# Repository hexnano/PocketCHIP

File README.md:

# PocketCHIP
PocketCHIP GSM+Camera Addon with A6C

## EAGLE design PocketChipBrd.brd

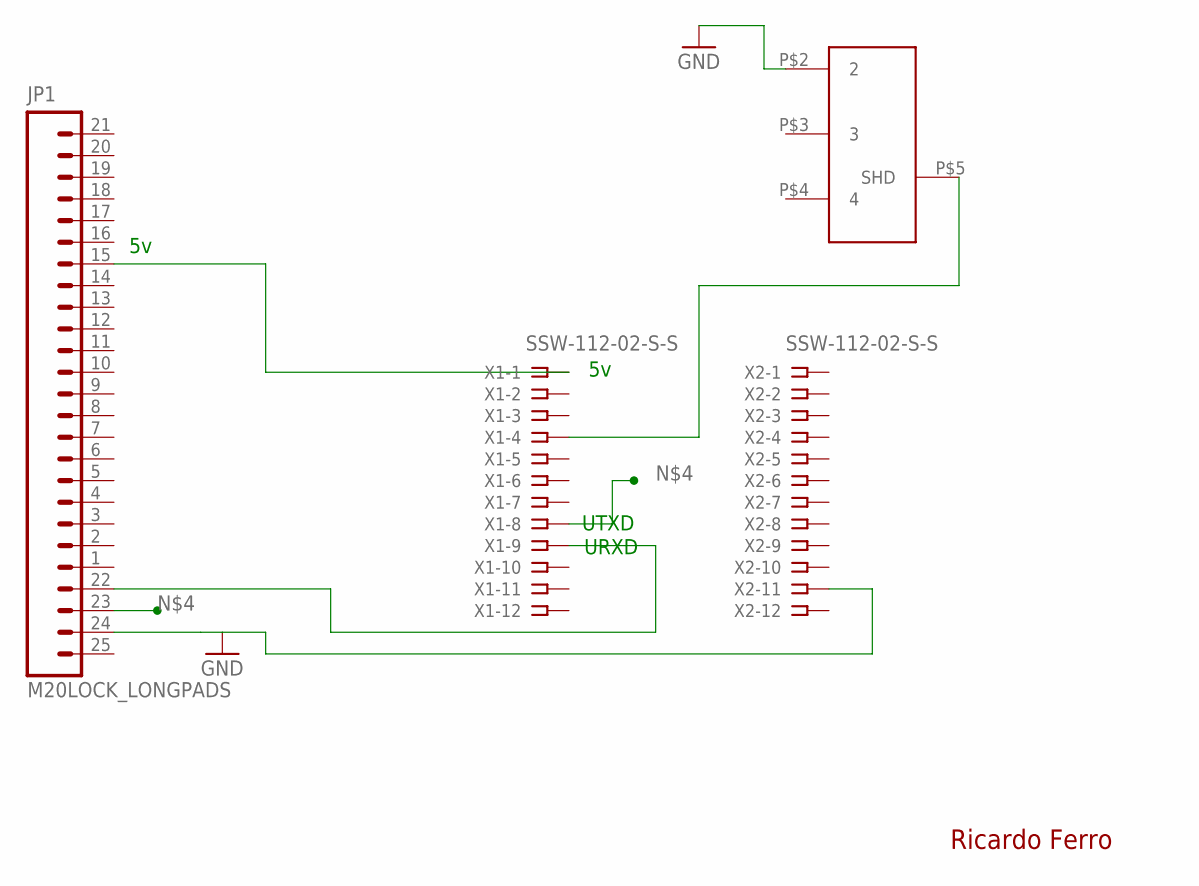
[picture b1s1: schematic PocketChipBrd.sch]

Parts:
JP1: M20LOCK_LONGPADS; 1X20_LOCK_LONGPADS
U$1: PJ-320D
X1, X2: SSW-112-02-S-S

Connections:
GND: JP1.24, U$1.P$2 (2), X2.11
unnamed: JP1.15, X1.1
unnamed: U$1.P$5 (SHD), X1.4
unnamed: JP1.22, X1.9
unnamed: JP1.23, X1.8

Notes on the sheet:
UTXD
URXD
Ricardo Ferro

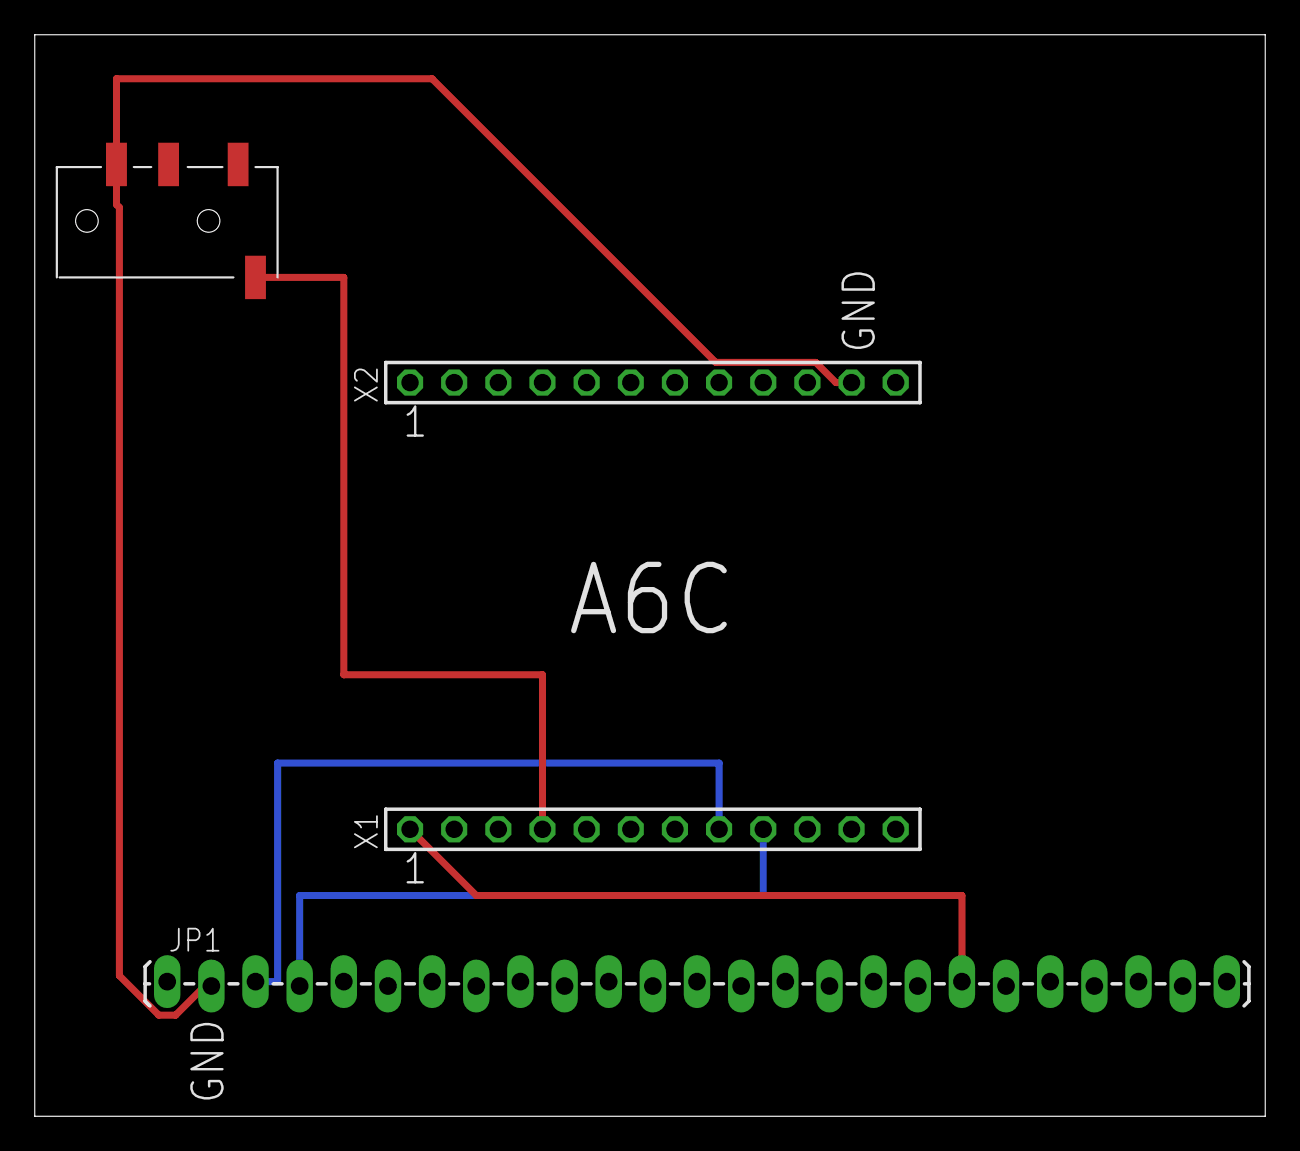
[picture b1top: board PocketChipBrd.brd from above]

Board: 2 copper layers, 70.8 x 62.2 mm, 4 parts (0 on the bottom side), 5 nets.
